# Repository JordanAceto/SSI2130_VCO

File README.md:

# SSI2130 based VCO PCB

## Features:
- Sine, Triangle, Sawtooth, and variable Pulse waves simultaneously available.
- All waveforms +/- 5vpp.
- Three 1 volt/octave inputs
- Through-zero linear FM
- Sync (choose hard or soft)
- PWM modulation inputs (choose triangle or saw input for the pulse wave)
- Designed to plug into a separate carrier pcb which houses the pots and jacks.

## [SCHEMATIC](https://github.com/JordanAceto/SSI2130_VCO/blob/main/construction_docs/SSI2130_VCO_schematic.pdf)

| Power rail | Current consumption |
|------|------|
| +12v | 30mA |
| -12v | 30mA |

## Status of the project:

Task | Status |
---------|--------------|
Schematic capture | &#9745;
PCB layout | &#9745;
Test build | &#9745;
Safe to order boards| &#9745;

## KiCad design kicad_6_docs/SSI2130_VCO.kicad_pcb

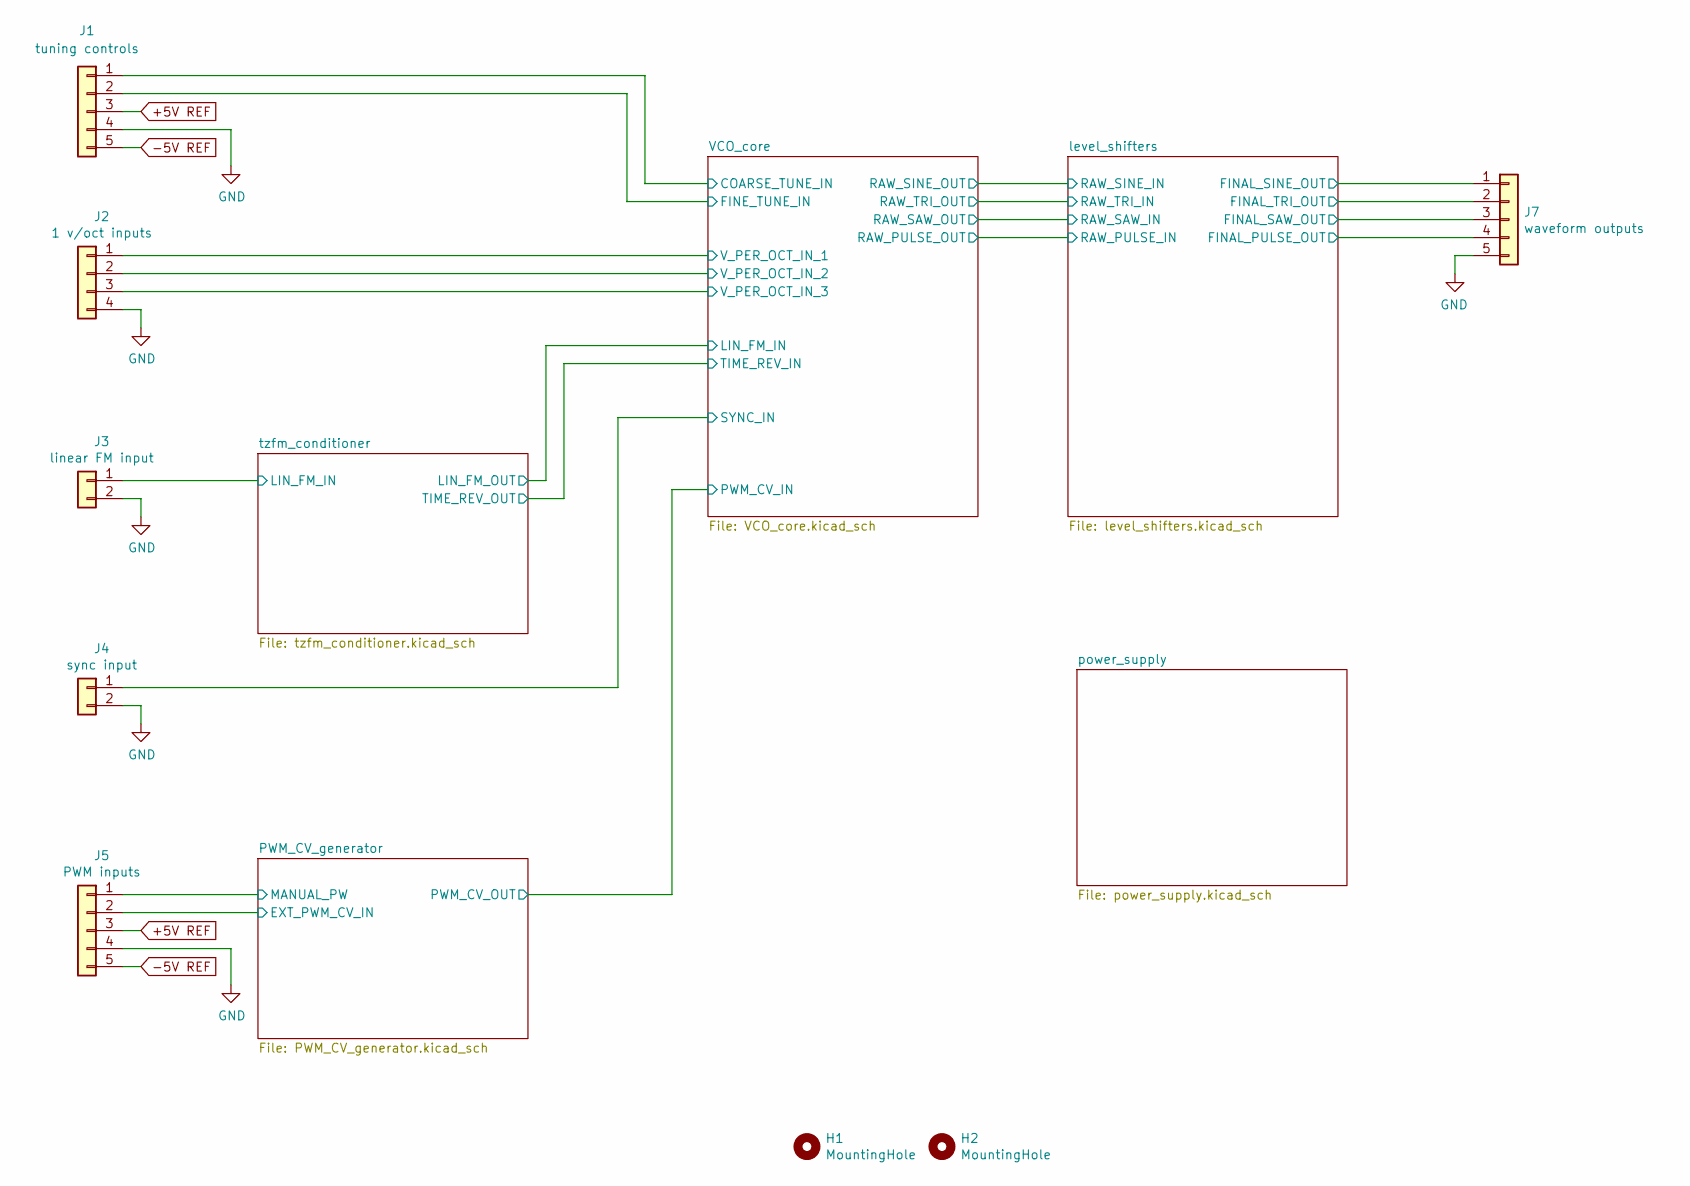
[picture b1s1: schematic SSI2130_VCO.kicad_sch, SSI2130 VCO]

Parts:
H1, H2: MountingHole; MountingHole_3.2mm_M3_DIN965_Pad
J1: tuning controls; PinHeader_1x05_P2.54mm_Vertical
J2: 1 v/oct inputs; PinHeader_1x04_P2.54mm_Vertical
J3: linear FM input; PinHeader_1x02_P2.54mm_Vertical
J4: sync input; PinHeader_1x02_P2.54mm_Vertical
J5: PWM inputs; PinHeader_1x05_P2.54mm_Vertical
J7: waveform outputs; PinHeader_1x05_P2.54mm_Vertical

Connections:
+5V REF: J1.3, J5.3; also elsewhere on the board
-5V REF: J1.5, J5.5; also elsewhere on the board
/PWM_CV_generator/EXT_PWM_CV_IN: J5.2; also elsewhere on the board
/PWM_CV_generator/MANUAL_PW: J5.1; also elsewhere on the board
/VCO_core/COARSE_TUNE_IN: J1.1; also elsewhere on the board
/VCO_core/FINE_TUNE_IN: J1.2; also elsewhere on the board
/VCO_core/SYNC_IN: J4.1; also elsewhere on the board
/VCO_core/V_PER_OCT_IN_1: J2.1; also elsewhere on the board
/VCO_core/V_PER_OCT_IN_2: J2.2; also elsewhere on the board
/VCO_core/V_PER_OCT_IN_3: J2.3; also elsewhere on the board
/level_shifters/FINAL_PULSE_OUT: J7.4; also elsewhere on the board
/level_shifters/FINAL_SAW_OUT: J7.3; also elsewhere on the board
/level_shifters/FINAL_SINE_OUT: J7.1; also elsewhere on the board
/level_shifters/FINAL_TRI_OUT: J7.2; also elsewhere on the board
/tzfm_conditioner/LIN_FM_IN: J3.1; also elsewhere on the board
GND: J1.4, J2.4, J3.2, J4.2, J5.4, J7.5; also elsewhere on the board

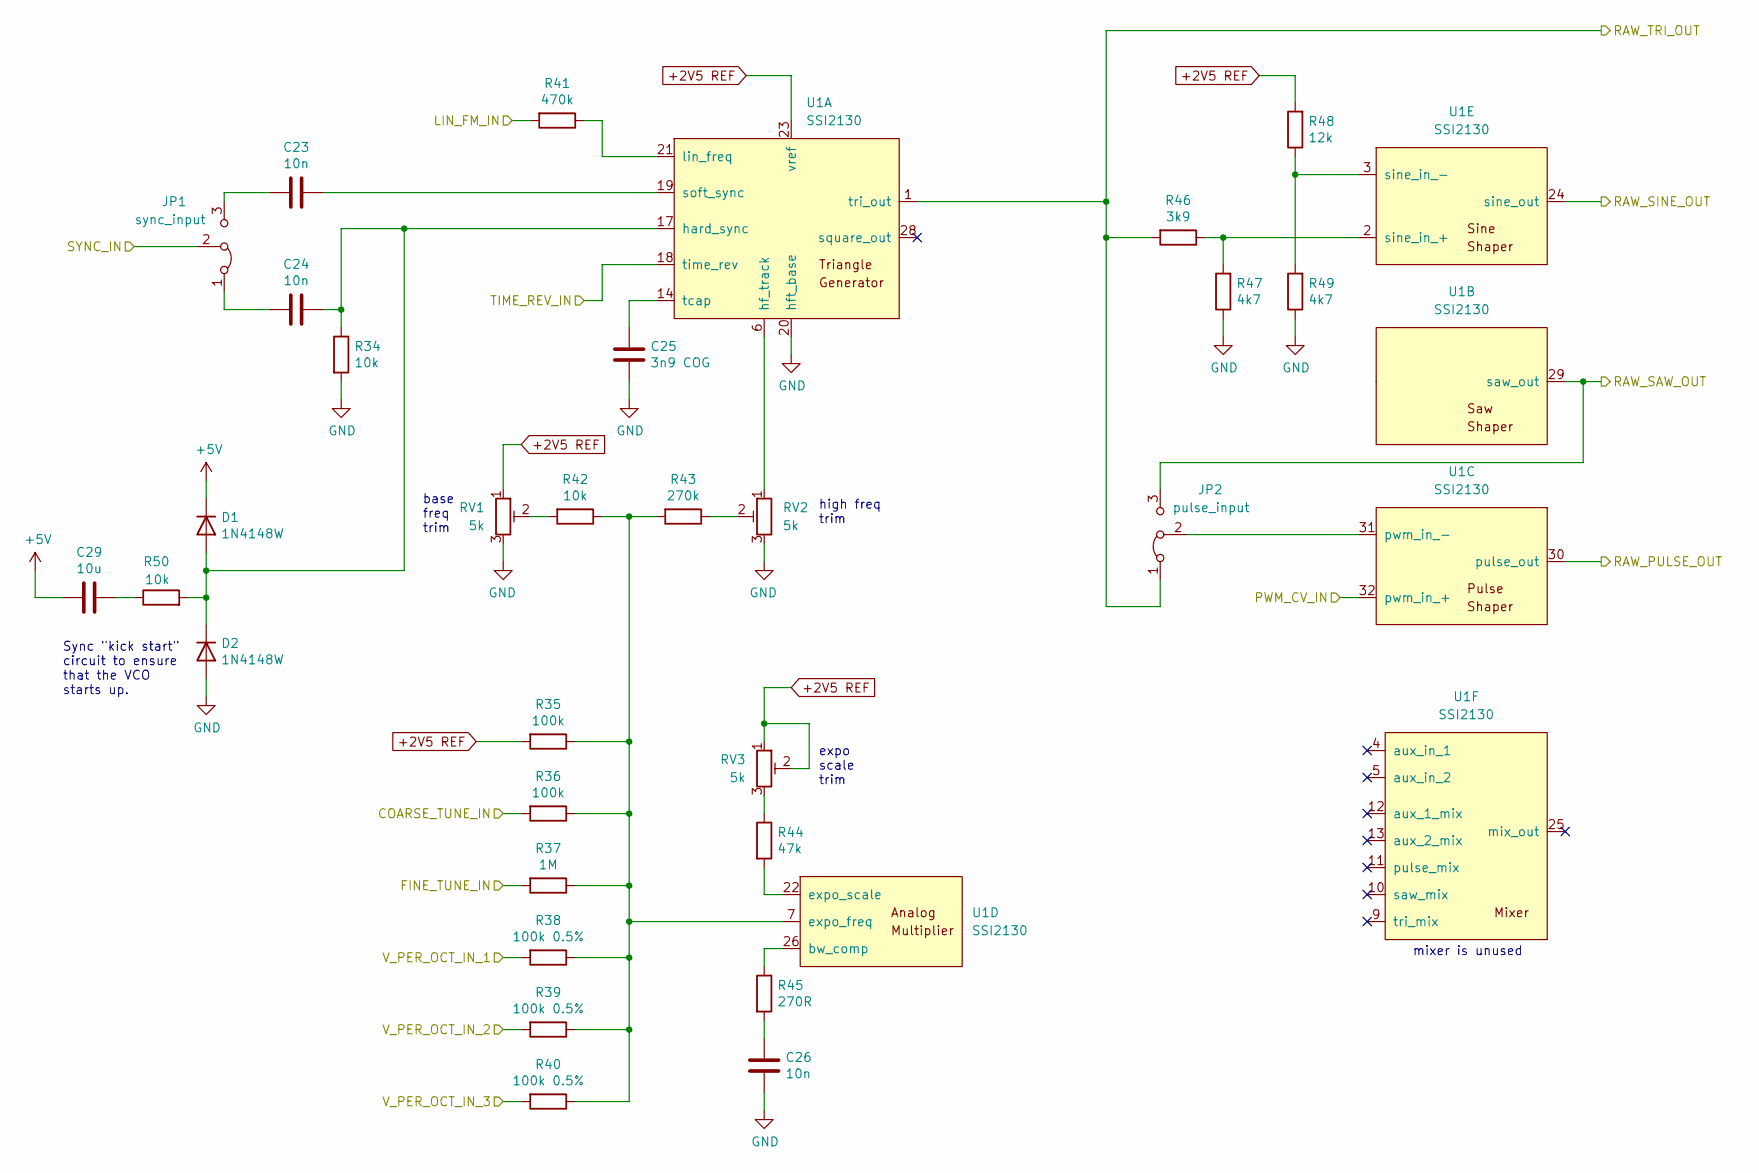
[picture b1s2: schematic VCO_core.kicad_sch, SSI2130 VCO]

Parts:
C23, C24, C26: 10n; C_0805_2012Metric
C25: 3n9 COG; C_0805_2012Metric
C29: 10u; C_0805_2012Metric
D1, D2: 1N4148W; D_SOD-123
JP1: sync_input; PinHeader_1x03_P2.54mm_Vertical
JP2: pulse_input; PinHeader_1x03_P2.54mm_Vertical
R34, R42, R50: 10k; R_0805_2012Metric
R35, R36: 100k; R_0805_2012Metric
R37: 1M; R_0805_2012Metric
R38, R39, R40: 100k 0.5%; R_0805_2012Metric
R41: 470k; R_0805_2012Metric
R43: 270k; R_0805_2012Metric
R44: 47k; R_0805_2012Metric
R45: 270R; R_0805_2012Metric
R46: 3k9; R_0805_2012Metric
R47, R49: 4k7; R_0805_2012Metric
R48: 12k; R_0805_2012Metric
RV1, RV2, RV3: 5k; Potentiometer_Bourns_3296W_Vertical
U1: SSI2130; PQN32_HandSoldering

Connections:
+2V5 REF: R35.2, R48.2, RV1.1, RV3.1, RV3.2, U1.23 (vref); also elsewhere on the board
+5V: C29.2, D1.1 (K); also elsewhere on the board
/PWM_CV_generator/PWM_CV_OUT: U1.32 (pwm_in_+); also elsewhere on the board
/VCO_core/COARSE_TUNE_IN: R36.2; also elsewhere on the board
/VCO_core/FINE_TUNE_IN: R37.2; also elsewhere on the board
/VCO_core/LIN_FM_IN: R41.2; also elsewhere on the board
/VCO_core/RAW_PULSE_OUT: U1.30 (pulse_out); also elsewhere on the board
/VCO_core/RAW_SAW_OUT: JP2.3 (B), U1.29 (saw_out); also elsewhere on the board
/VCO_core/RAW_SINE_OUT: U1.24 (sine_out); also elsewhere on the board
/VCO_core/RAW_TRI_OUT: JP2.1 (A), R46.2, U1.1 (tri_out); also elsewhere on the board
/VCO_core/SYNC_IN: JP1.2 (C); also elsewhere on the board
/VCO_core/TIME_REV_IN: U1.18 (time_rev); also elsewhere on the board
/VCO_core/V_PER_OCT_IN_1: R38.2; also elsewhere on the board
/VCO_core/V_PER_OCT_IN_2: R39.2; also elsewhere on the board
/VCO_core/V_PER_OCT_IN_3: R40.2; also elsewhere on the board
GND: C25.2, C26.2, D2.2 (A), R34.2, R47.1, R49.1, RV1.3, RV2.3, U1.20 (hft_base); also elsewhere on the board
unnamed: C23.1, U1.19 (soft_sync)
unnamed: C23.2, JP1.3 (B)
unnamed: C24.1, D1.2 (A), D2.1 (K), R34.1, R50.2, U1.17 (hard_sync)
unnamed: C24.2, JP1.1 (A)
unnamed: C25.1, U1.14 (tcap)
unnamed: C26.1, R45.2
unnamed: C29.1, R50.1
unnamed: JP2.2 (C), U1.31 (pwm_in_-)
unnamed: R35.1, R36.1, R37.1, R38.1, R39.1, R40.1, R42.1, R43.2, U1.7 (expo_freq)
unnamed: R41.1, U1.21 (lin_freq)
unnamed: R42.2, RV1.2
unnamed: R43.1, RV2.2
unnamed: R44.1, RV3.3
unnamed: R44.2, U1.22 (expo_scale)
unnamed: R45.1, U1.26 (bw_comp)
unnamed: R46.1, R47.2, U1.2 (sine_in_+)
unnamed: R48.1, R49.2, U1.3 (sine_in_-)
unnamed: RV2.1, U1.6 (hf_track)

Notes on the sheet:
base freq trim
mixer is unused
Sync "kick start" circuit to ensure that the VCO starts up.
expo scale trim
high freq trim

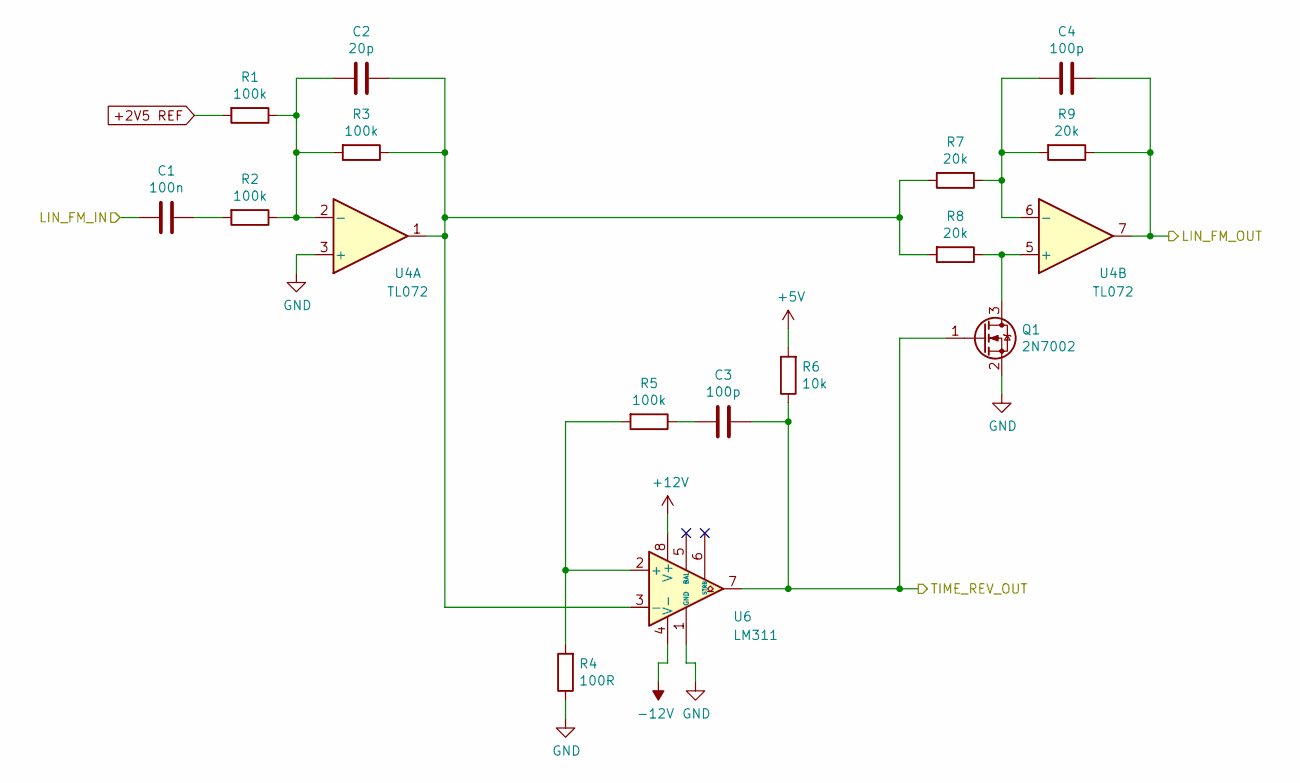
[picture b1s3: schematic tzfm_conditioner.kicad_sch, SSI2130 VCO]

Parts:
C1: 100n; C_0805_2012Metric
C2: 20p; C_0805_2012Metric
C3, C4: 100p; C_0805_2012Metric
Q1: 2N7002; SOT-23
R1, R2, R3, R5: 100k; R_0805_2012Metric
R4: 100R; R_0805_2012Metric
R6: 10k; R_0805_2012Metric
R7, R8, R9: 20k; R_0805_2012Metric
U4: TL072; SOIC-8_3.9x4.9mm_P1.27mm
U6: LM311; SOIC-8_3.9x4.9mm_P1.27mm

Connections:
+2V5 REF: R1.2; also elsewhere on the board
+5V: R6.2; also elsewhere on the board
+12V: U6.8 (V+); also elsewhere on the board
-12V: U6.4 (V-); also elsewhere on the board
/VCO_core/LIN_FM_IN: C4.1, R9.1, U4.7; also elsewhere on the board
/VCO_core/TIME_REV_IN: C3.1, Q1.1 (G), R6.1, U6.7; also elsewhere on the board
/tzfm_conditioner/LIN_FM_IN: C1.2; also elsewhere on the board
GND: Q1.2 (S), R4.1, U4.3 (+), U6.1 (GND); also elsewhere on the board
unnamed: C1.1, R2.2
unnamed: C2.1, R3.1, R7.2, R8.2, U4.1, U6.3 (-)
unnamed: C2.2, R1.1, R2.1, R3.2, U4.2 (-)
unnamed: C3.2, R5.1
unnamed: C4.2, R7.1, R9.2, U4.6 (-)
unnamed: Q1.3 (D), R8.1, U4.5 (+)
unnamed: R4.2, R5.2, U6.2 (+)

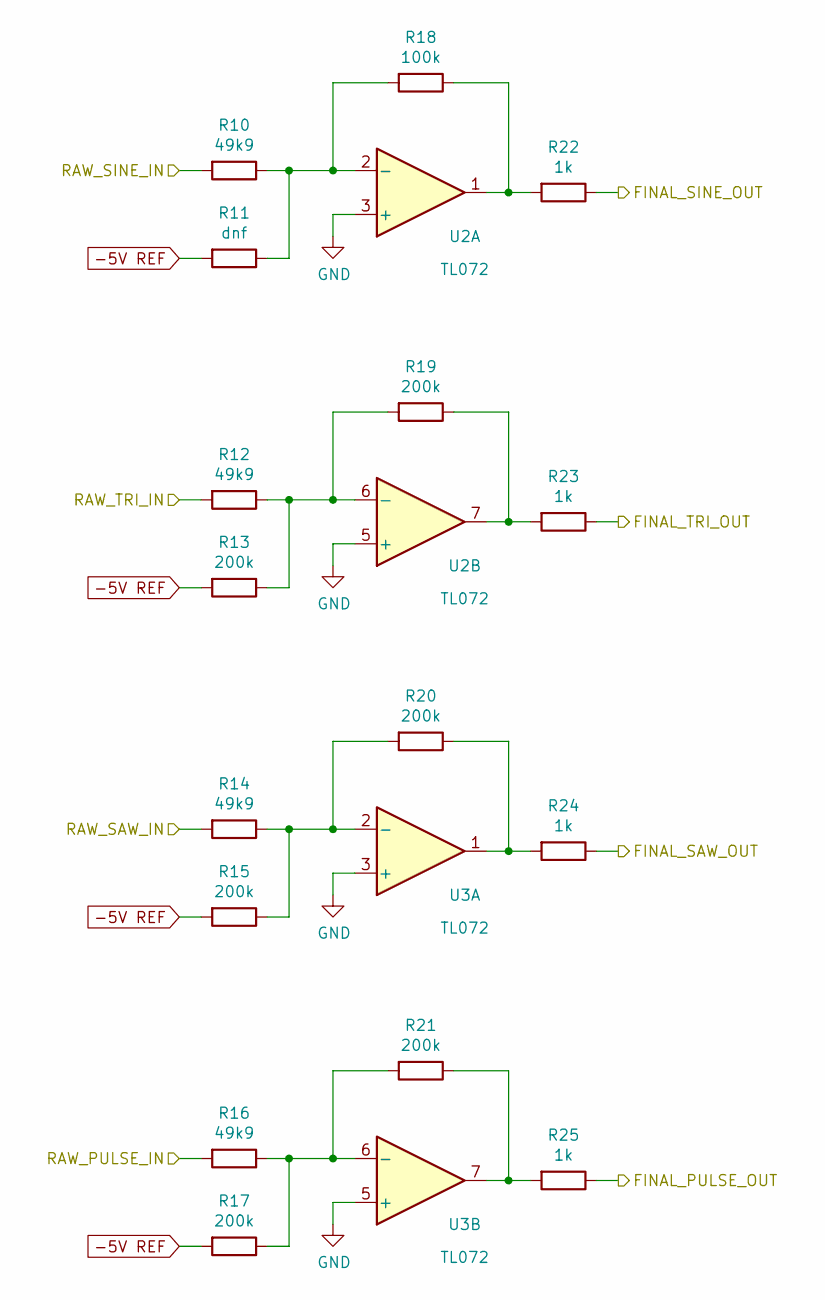
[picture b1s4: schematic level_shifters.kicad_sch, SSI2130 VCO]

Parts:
R10, R12, R14, R16: 49k9; R_0805_2012Metric
R11: dnf; R_0805_2012Metric
R13, R15, R17, R19, R20, R21: 200k; R_0805_2012Metric
R18: 100k; R_0805_2012Metric
R22, R23, R24, R25: 1k; R_0805_2012Metric
U2, U3: TL072; SOIC-8_3.9x4.9mm_P1.27mm

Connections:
-5V REF: R11.2, R13.2, R15.2, R17.2; also elsewhere on the board
/VCO_core/RAW_PULSE_OUT: R16.2; also elsewhere on the board
/VCO_core/RAW_SAW_OUT: R14.2; also elsewhere on the board
/VCO_core/RAW_SINE_OUT: R10.2; also elsewhere on the board
/VCO_core/RAW_TRI_OUT: R12.2; also elsewhere on the board
/level_shifters/FINAL_PULSE_OUT: R25.1; also elsewhere on the board
/level_shifters/FINAL_SAW_OUT: R24.1; also elsewhere on the board
/level_shifters/FINAL_SINE_OUT: R22.1; also elsewhere on the board
/level_shifters/FINAL_TRI_OUT: R23.1; also elsewhere on the board
GND: U2.3 (+), U2.5 (+), U3.3 (+), U3.5 (+); also elsewhere on the board
unnamed: R10.1, R11.1, R18.2, U2.2 (-)
unnamed: R12.1, R13.1, R19.2, U2.6 (-)
unnamed: R14.1, R15.1, R20.2, U3.2 (-)
unnamed: R16.1, R17.1, R21.2, U3.6 (-)
unnamed: R18.1, R22.2, U2.1
unnamed: R19.1, R23.2, U2.7
unnamed: R20.1, R24.2, U3.1
unnamed: R21.1, R25.2, U3.7

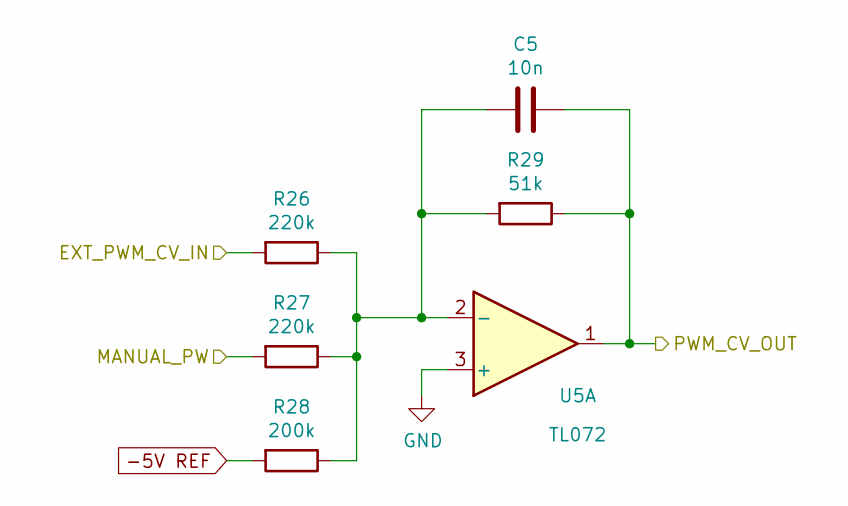
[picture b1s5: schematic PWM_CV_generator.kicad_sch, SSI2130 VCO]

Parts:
C5: 10n; C_0805_2012Metric
R26, R27: 220k; R_0805_2012Metric
R28: 200k; R_0805_2012Metric
R29: 51k; R_0805_2012Metric
U5: TL072; SOIC-8_3.9x4.9mm_P1.27mm

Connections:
-5V REF: R28.2; also elsewhere on the board
/PWM_CV_generator/EXT_PWM_CV_IN: R26.2; also elsewhere on the board
/PWM_CV_generator/MANUAL_PW: R27.2; also elsewhere on the board
/PWM_CV_generator/PWM_CV_OUT: C5.1, R29.1, U5.1; also elsewhere on the board
GND: U5.3 (+); also elsewhere on the board
unnamed: C5.2, R26.1, R27.1, R28.1, R29.2, U5.2 (-)

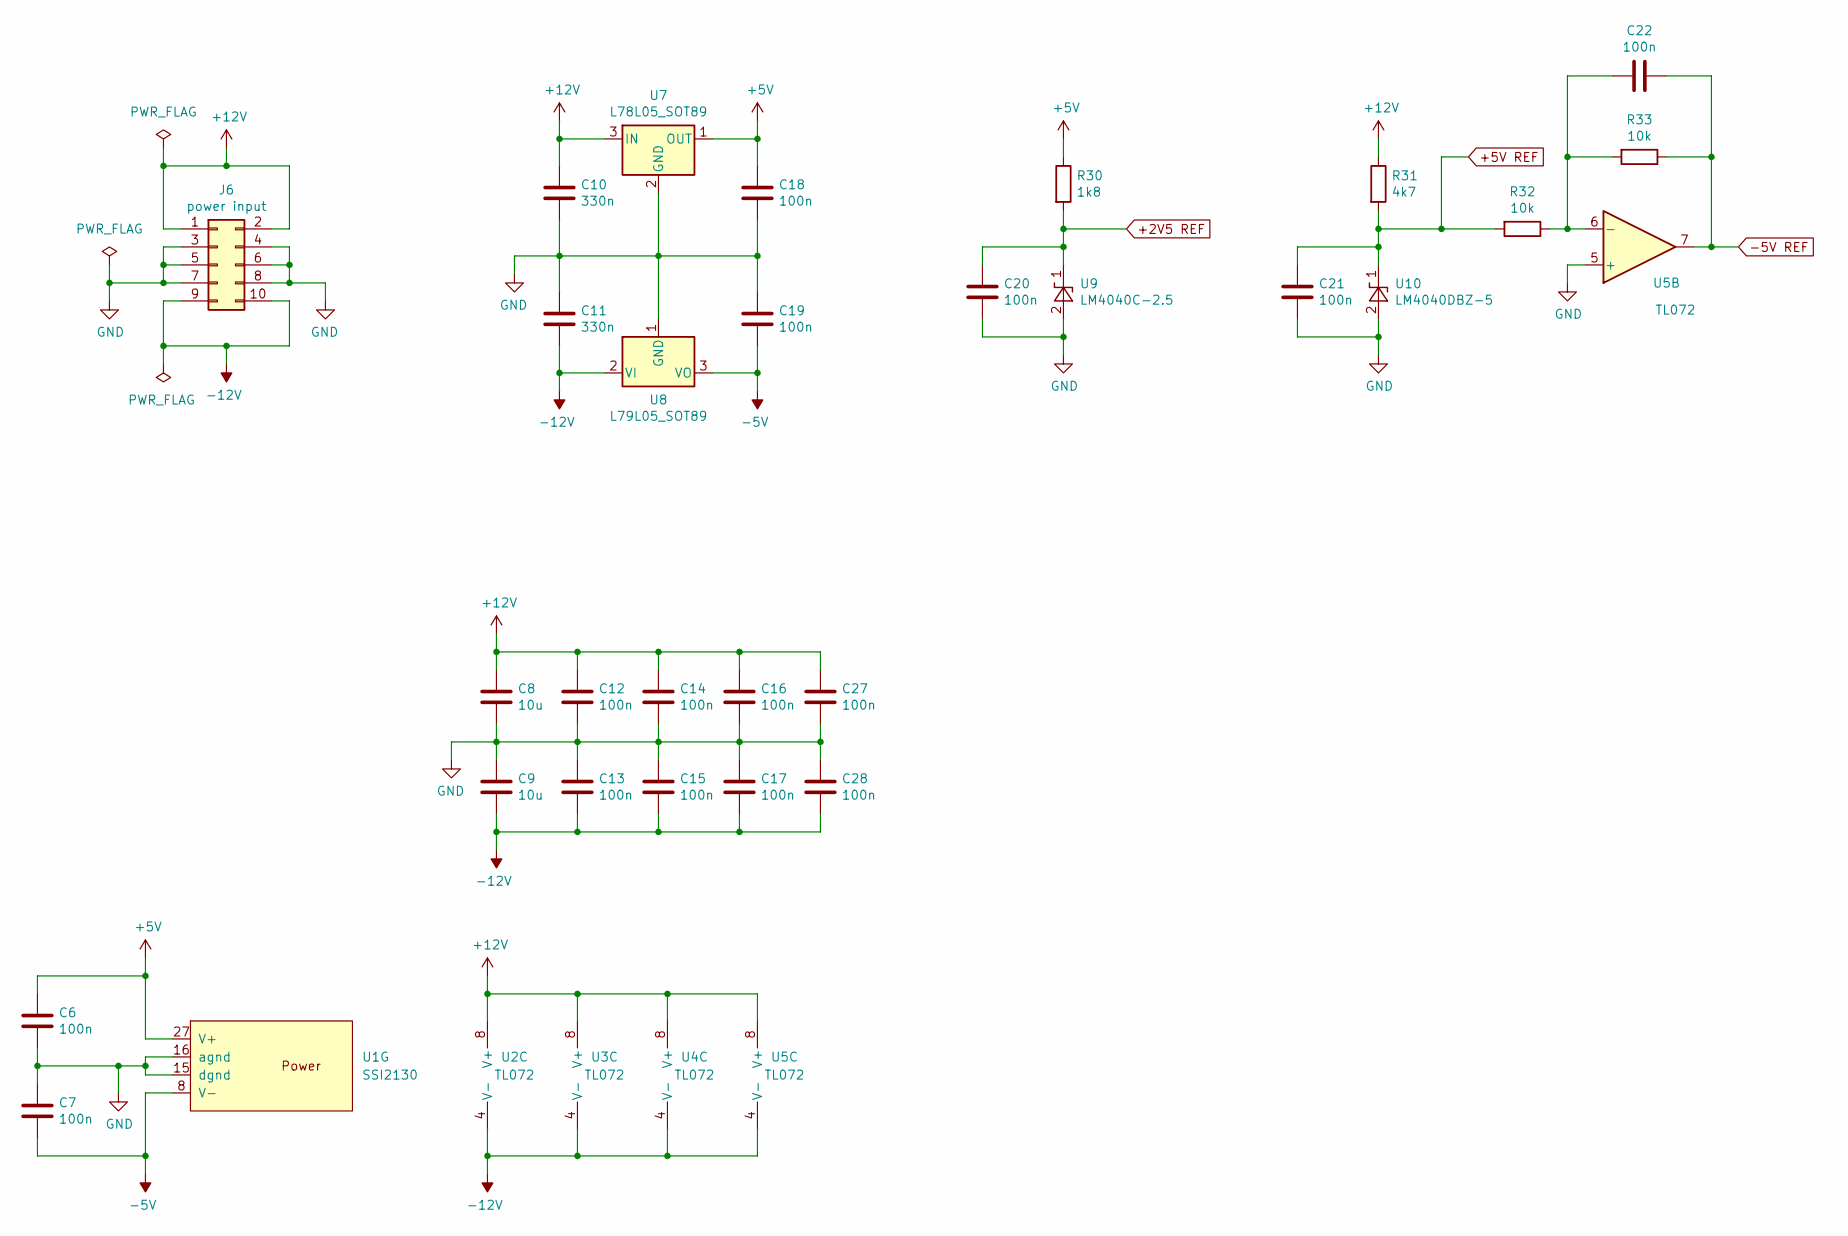
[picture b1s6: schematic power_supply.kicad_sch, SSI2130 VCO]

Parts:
C6, C7, C12, C13, C14, C15, C16, C17, C18, C19, C20, C21, C22, C27, C28: 100n; C_0805_2012Metric
C8, C9: 10u; C_0805_2012Metric
C10, C11: 330n; C_0805_2012Metric
J6: power input; PinHeader_2x05_P2.54mm_Vertical
R30: 1k8; R_0805_2012Metric
R31: 4k7; R_0805_2012Metric
R32, R33: 10k; R_0805_2012Metric
U1: SSI2130; PQN32_HandSoldering
U2, U3, U4, U5: TL072; SOIC-8_3.9x4.9mm_P1.27mm
U7: L78L05_SOT89; SOT-89-3
U8: L79L05_SOT89; SOT-89-3
U9: LM4040C-2.5; SOT-23
U10: LM4040DBZ-5; SOT-23

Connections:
+2V5 REF: C20.1, R30.2, U9.1 (K); also elsewhere on the board
+5V: C6.1, C18.1, R30.1, U1.27 (V+), U7.1 (OUT); also elsewhere on the board
+5V REF: C21.1, R31.2, R32.2, U10.1 (K); also elsewhere on the board
+12V: C8.1, C10.1, C12.1, C14.1, C16.1, C27.1, J6.1, J6.2, R31.1, U2.8 (V+), U3.8 (V+), U4.8 (V+), U5.8 (V+), U7.3 (IN); also elsewhere on the board
-5V: C7.2, C19.2, U1.8 (V-), U8.3 (VO)
-5V REF: C22.1, R33.1, U5.7; also elsewhere on the board
-12V: C9.2, C11.2, C13.2, C15.2, C17.2, C28.2, J6.9, J6.10, U2.4 (V-), U3.4 (V-), U4.4 (V-), U5.4 (V-), U8.2 (VI); also elsewhere on the board
GND: C6.2, C7.1, C8.2, C9.1, C10.2, C11.1, C12.2, C13.1, C14.2, C15.1, C16.2, C17.1, C18.2, C19.1, C20.2, C21.2, C27.2, C28.1, J6.3, J6.4, J6.5, J6.6, J6.7, J6.8, U1.15 (dgnd), U1.16 (agnd), U5.5 (+), U7.2 (GND), U8.1 (GND), U9.2 (A), U10.2 (A); also elsewhere on the board
unnamed: C22.2, R32.1, R33.2, U5.6 (-)

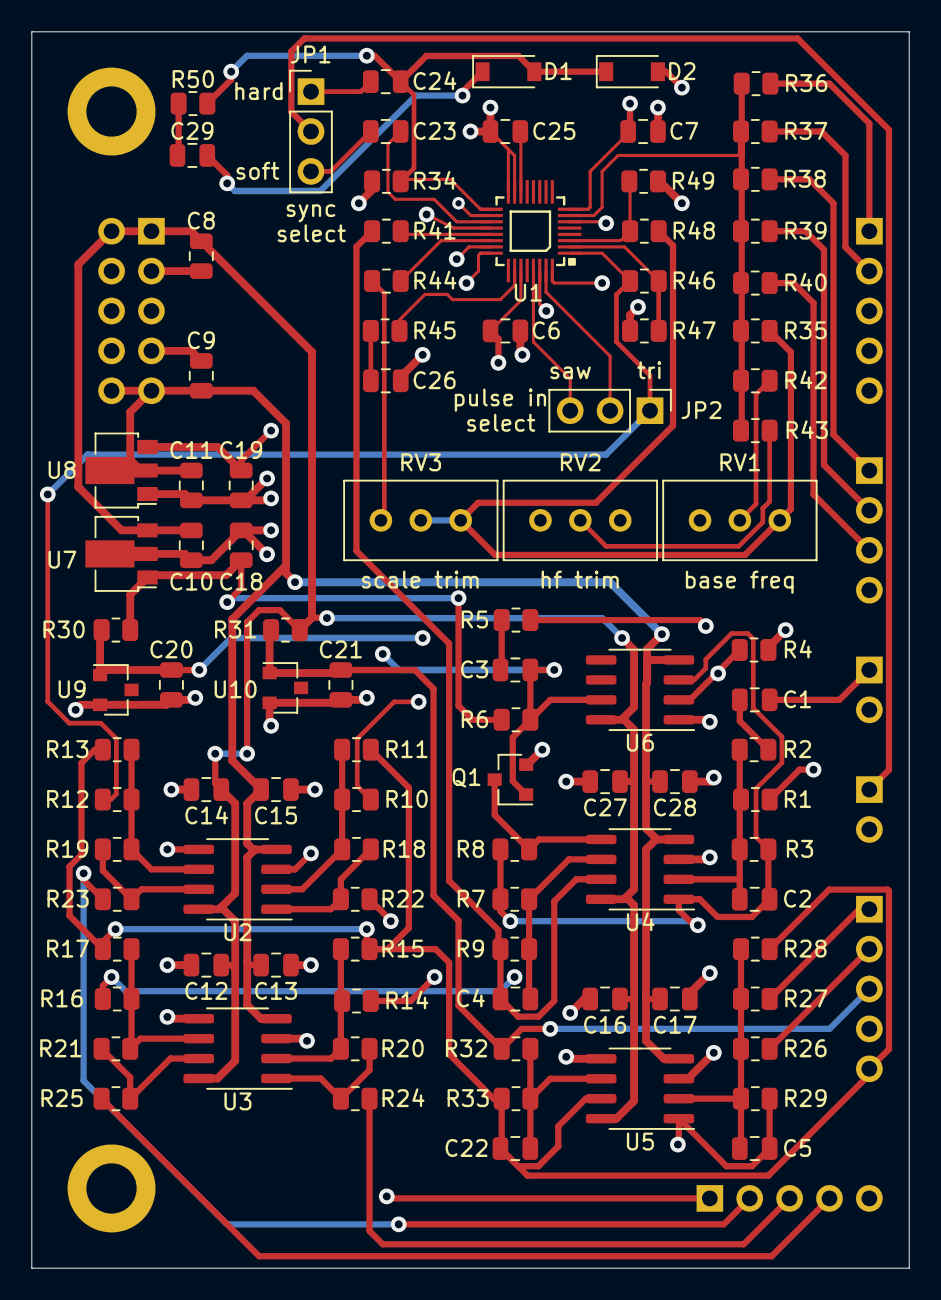
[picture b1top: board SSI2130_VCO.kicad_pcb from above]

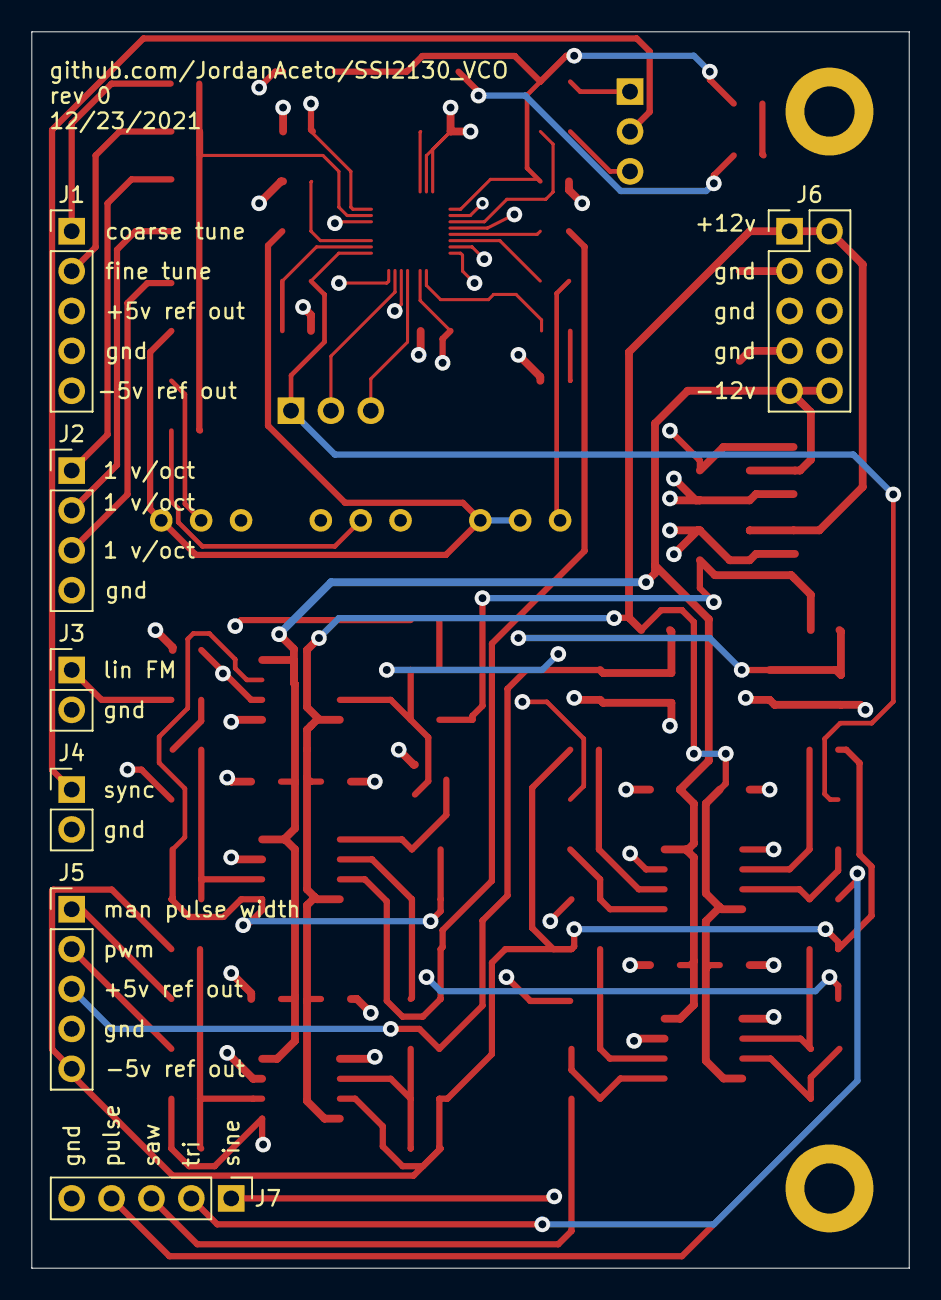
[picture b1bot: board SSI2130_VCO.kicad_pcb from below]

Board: 4 copper layers, 55.9 x 78.7 mm, 106 parts (7 on the bottom side), 63 nets.

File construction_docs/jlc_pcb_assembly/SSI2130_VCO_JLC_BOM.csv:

Comment,Designator, Footprint,LCSC Part Number
100n,C1 C6 C7 C12 C13 C14 C15 C16 C17 C18 C19 C20 C21 C22 C27 C28 ,0805,C49678
330n,C10 C11 ,0805,C1740
20p,C2 ,0805,C1798
10n,C23 C24 C26 ,0805,C1710
100p,C3 C4 ,0805,C1790
1n,C5 ,0805,C46653
10u,C8 C9 C29,0805,C440198
2N7002,Q1 ,SOT-23-3,C8545
49k9,R10 R12 R14 R16 ,0805,C17719
1k,R22 R23 R24 R25 ,0805,C17513
220k,R26 R27 ,0805,C17556
200k,R13 R15 R17 R19 R20 R21 R28 ,0805,C17539
51k,R29 ,0805,C17737
100k,R1 R2 R3 R5 R18 R35 R36 ,0805,C17407
1k8,R30 ,0805,C17398
1M,R37 ,0805,C17514
100R,R4 ,0805,C17408
470k,R41 ,0805,C17709
270k,R43 ,0805,C17589
47k,R44 ,0805,C17713
270R,R45 ,0805,C17590
3k9,R46 ,0805,C17614
4k7,R31 R47 R49 ,0805,C17673
12k,R48 ,0805,C17444
10k,R6 R32 R33 R34 R42 R50,0805,C17414
20k,R7 R8 R9 ,0805,C4328
TL072,U2 U3 U4 U5 ,SOIC-8_3.9x4.9x1.27p,C6961
1N4048W,D1 D2,SOD-123,C81598

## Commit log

2021-12-23 fix schematic link
2021-12-23 reduce amt of weird resistor vals
2021-12-23 fix pic path
2021-12-23 fix error where wires were crossed
2021-12-24 add kick-start network to ensure start up
2022-01-28 check boxes after successful test build
2022-06-04 Update gitignore
2022-06-04 Update to KiCad 6, tweak SSI2130 symbol

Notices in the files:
kicad_6_docs/PWM_CV_generator.kicad_sch:
creativecommons.org/licenses/by/4.0
License: CC by 4.0
